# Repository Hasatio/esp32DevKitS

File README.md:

# ESP32-DEVKIT-S

The circuit taken as an example while designing the board [Thing Plus C - ESP32 WROOM](https://www.sparkfun.com/products/retired/18018)

This pcb scaled down using the components in the example schematic

## Revision 0

### Added:

- 1x ADXL345 (Accelerometer)
- 2x 1x20 FPC connector for ESP pins
- In breakable PCB:
  - 4x ADS1115 (Analog to Digital Converter)
  - 1x20 FPC connector
  - 1x QWIIC connector

### Changed:

- ESP32-WROOM-32D model
- Battery socket breakable PCB
- Logo

### Removed:

- RGB led
- SD card

### Note: The connection cannot be made because the tx rx connection paths are not correct.

## Revision 1

- Two circuits were produced for the left and right foot.

### Added:
- New circuit in mirror image design

### Changed:
- Circuit design, components in usb communication and components in the power section
- CH340C model
- TX, RX connection paths reversed
- Analog pull up resistor 100k

### Note: The battery does not charge when the switch is in the off position.

## Revision 2

### Changed:
- The on/off switch will only be used for battery discharge

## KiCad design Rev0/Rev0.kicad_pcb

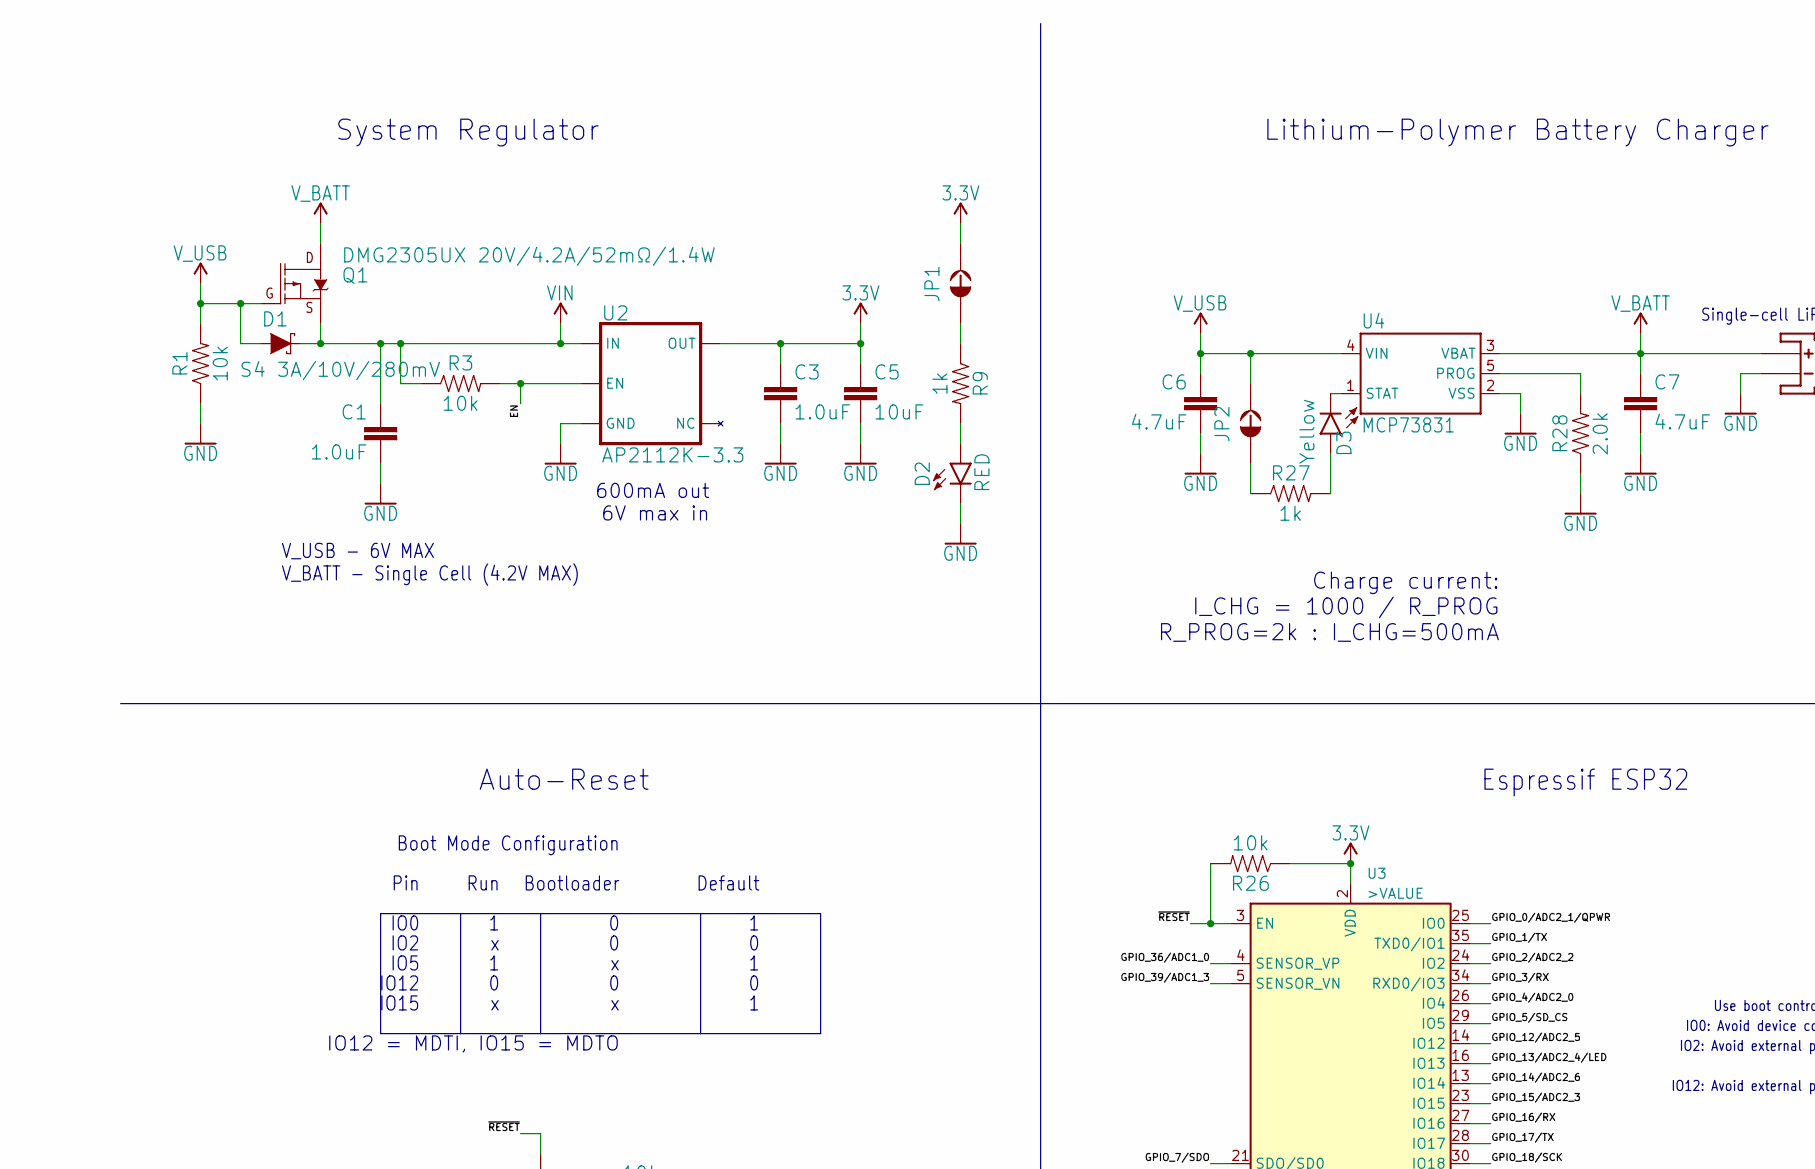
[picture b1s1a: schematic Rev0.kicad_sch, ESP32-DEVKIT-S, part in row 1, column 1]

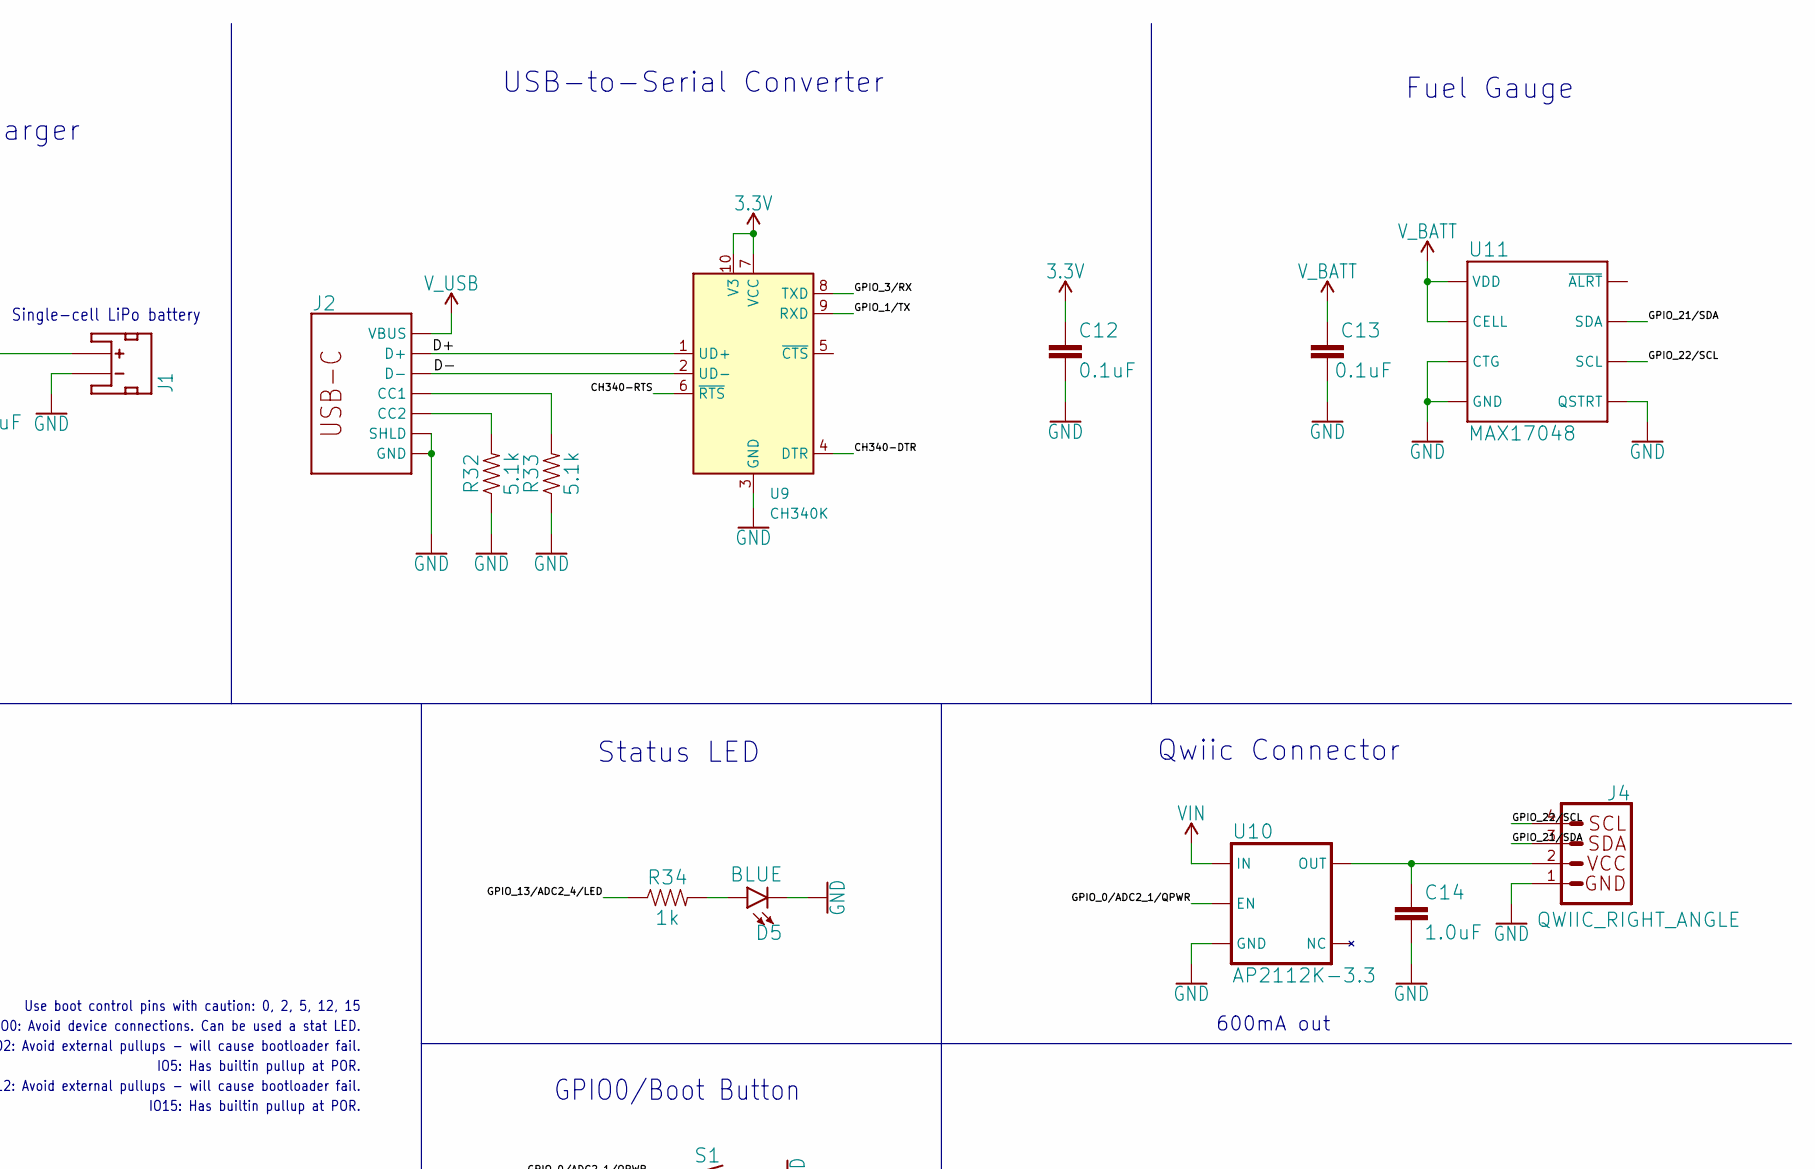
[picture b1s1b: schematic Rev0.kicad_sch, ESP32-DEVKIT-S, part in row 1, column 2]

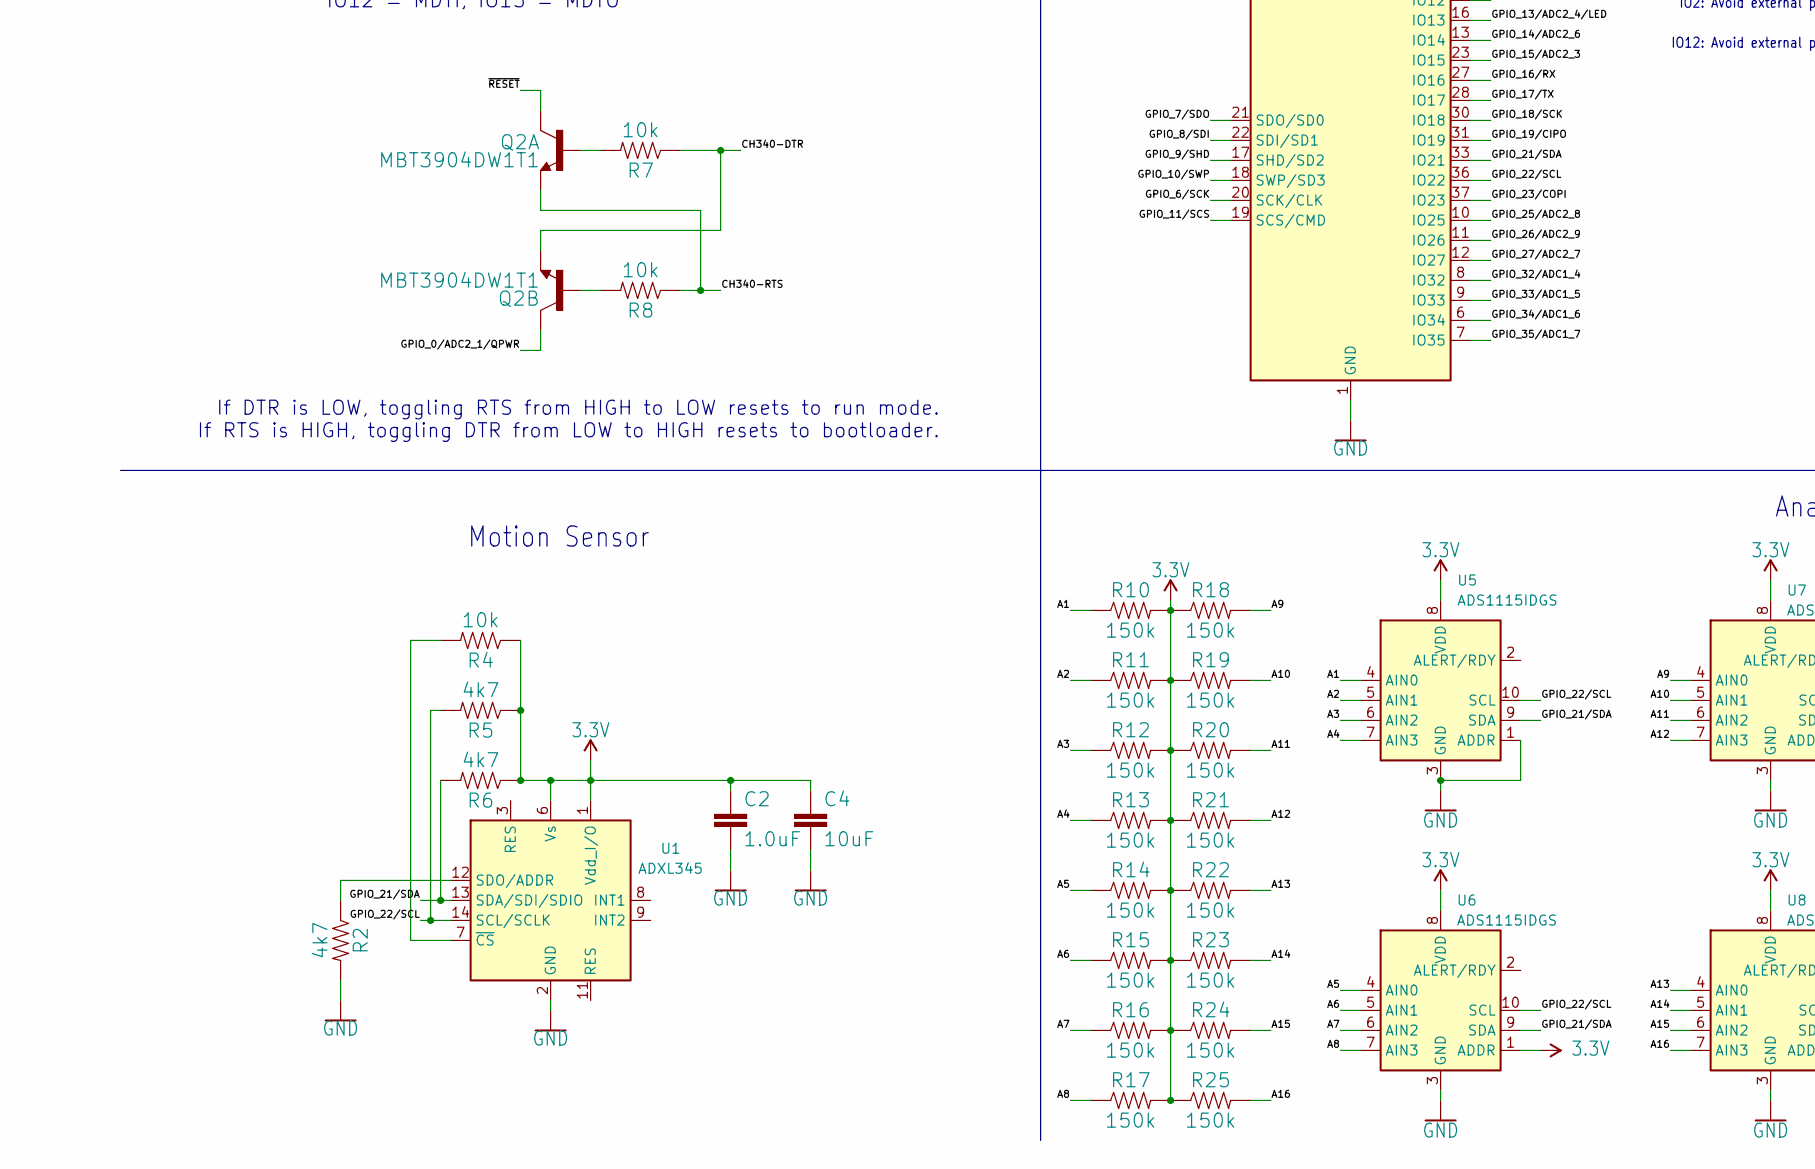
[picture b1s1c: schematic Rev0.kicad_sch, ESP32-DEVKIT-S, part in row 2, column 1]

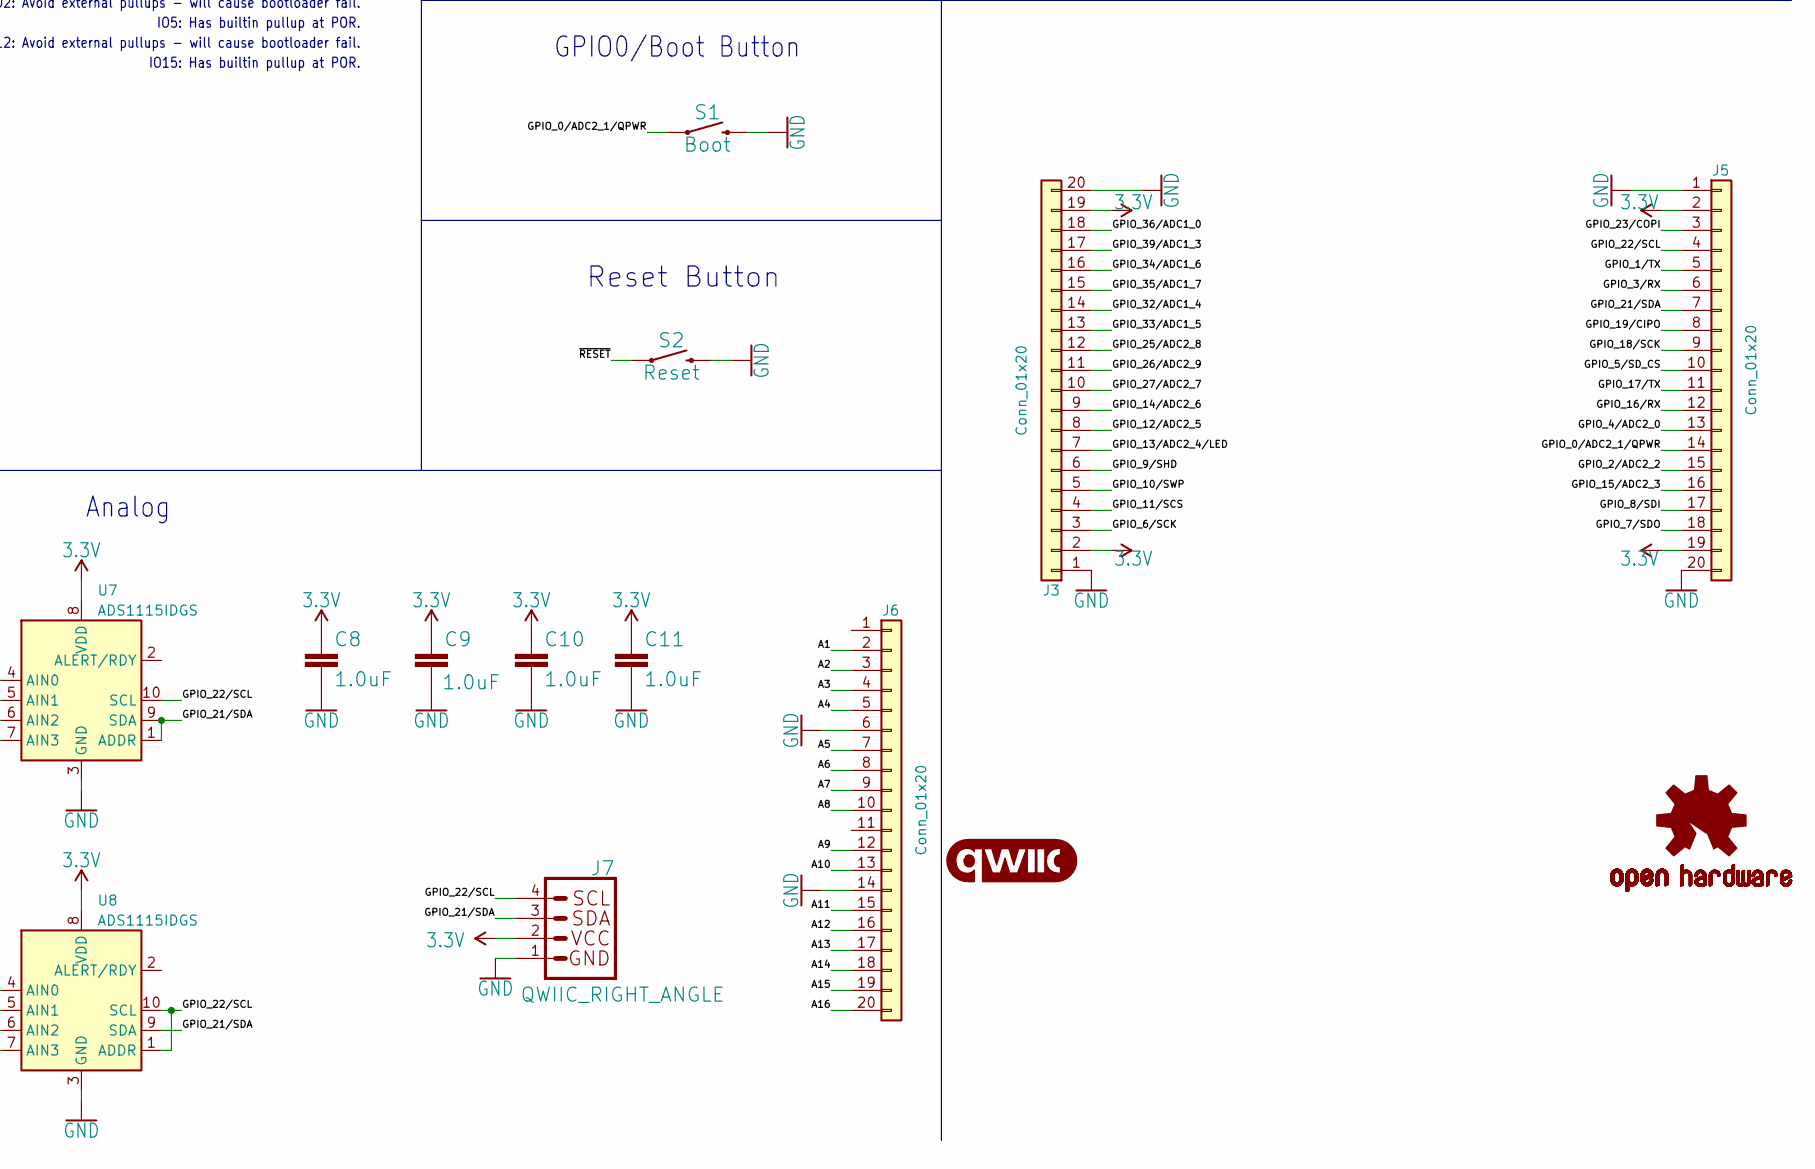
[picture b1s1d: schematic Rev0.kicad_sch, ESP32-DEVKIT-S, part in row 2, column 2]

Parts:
C1, C2, C3, C8, C9, C10, C11, C14: 1.0uF; 0402-TIGHT
C4, C5: 10uF; 0402-TIGHT
C6, C7: 4.7uF; 0402-TIGHT
C12, C13: 0.1uF; 0402-TIGHT
D1: S4 3A/10V/280mV; SOD-323
D2: RED; LED-0603
D3: Yellow; LED-0603
D5: BLUE; LED-0603
J1: JST_2MM_MALE; JST-2-SMD
J2: USB_C_2-LAYER_PADS; USB-C-16P-2LAYER-PADS
J3, J5, J6: Conn_01x20; Molex_200528-0200_1x20-1MP_P1.00mm_Horizontal
J4, J7: QWIIC_RIGHT_ANGLE; JST04_1MM_RA
JP1, JP2: JUMPER-SMT_2_NC_TRACE_SILK; SMT-JUMPER_2_NC_TRACE_SILK
LOGO1: QWIIC_LOGO_4MM; QWIIC_4MM
LOGO2: OSHW-LOGOMINI; OSHW-LOGO-MINI
Q1: DMG2305UX 20V/4.2A/52mΩ/1.4W; SOT23-3
Q2: MBT3904DW1T1; SC70-6
R1, R3, R4, R7, R8, R26: 10k; 0402-TIGHT
R2, R5, R6: 4k7; 0402-TIGHT
R9, R27, R34: 1k; 0402-TIGHT
R10, R11, R12, R13, R14, R15, R16, R17, R18, R19, R20, R21, R22, R23, R24, R25: 150k; 0402-TIGHT
R28: 2.0k; 0402-TIGHT
R32, R33: 5.1k; 0402-TIGHT
S1: Boot; TACTILE_SWITCH_SMD_4.6X2.8MM
S2: Reset; TACTILE_SWITCH_SMD_4.6X2.8MM
U1: ADXL345; LGA-14_3x5mm_P0.8mm_LayoutBorder1x6y
U2, U10: SOT23-5
U3: >VALUE; ESP-WROOM-32-NARROW
U4: MCP73831; SOT23-5
U5, U6, U7, U8: ADS1115IDGS; TSSOP-10_3x3mm_P0.5mm
U9: CH340K; SSOP-10_3.9x4.9mm_P1.00mm
U11: MAX17048; DFN-8

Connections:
3.3V: C2.1, C3.1, C4.1, C5.1, C8.1, C9.1, C10.1, C11.1, C12.1, J3.2, J3.19, J5.2, J5.19, J7.2, JP1.2, R4.1, R5.1, R6.1, R10.2, R11.2, R12.2, R13.2, R14.2, R15.2, R16.2, R17.2, R18.1, R19.1, R20.1, R21.1, R22.1, R23.1, R24.1, R25.1, R26.1, U1.1 (Vdd_I/O), U1.6 (Vs), U2.5 (OUT), U3.2 (VDD), U5.8 (VDD), U6.1 (ADDR), U6.8 (VDD), U7.8 (VDD), U8.8 (VDD), U9.7 (VCC), U9.10 (V3); also elsewhere on the board
/A1: J6.2, R10.1, U5.4 (AIN0); also elsewhere on the board
/A2: J6.3, R11.1, U5.5 (AIN1); also elsewhere on the board
/A3: J6.4, R12.1, U5.6 (AIN2); also elsewhere on the board
/A4: J6.5, R13.1, U5.7 (AIN3); also elsewhere on the board
/A5: J6.7, R14.1, U6.4 (AIN0); also elsewhere on the board
/A6: J6.8, R15.1, U6.5 (AIN1); also elsewhere on the board
/A7: J6.9, R16.1, U6.6 (AIN2); also elsewhere on the board
/A8: J6.10, R17.1, U6.7 (AIN3); also elsewhere on the board
/A9: J6.12, R18.2, U7.4 (AIN0); also elsewhere on the board
/A10: J6.13, R19.2, U7.5 (AIN1); also elsewhere on the board
/A11: J6.15, R20.2, U7.6 (AIN2); also elsewhere on the board
/A12: J6.16, R21.2, U7.7 (AIN3); also elsewhere on the board
/A13: J6.17, R22.2, U8.4 (AIN0); also elsewhere on the board
/A14: J6.18, R23.2, U8.5 (AIN1); also elsewhere on the board
/A15: J6.19, R24.2, U8.6 (AIN2); also elsewhere on the board
/A16: J6.20, R25.2, U8.7 (AIN3); also elsewhere on the board
/CH340-DTR: Q2.1 (E), R7.1, U9.4 (DTR)
/CH340-RTS: Q2.4 (E), R8.1, U9.6 (~RTS)
/D+: J2.A6 (D+), J2.B6 (D+), U9.1 (UD+)
/D-: J2.A7 (D-), J2.B7 (D-), U9.2 (UD-)
/EN: R3.2, U2.3 (EN)
/GPIO_0/ADC2_1/QPWR: J5.14, Q2.6 (C), S1.1, S1.2 (1), U3.25 (IO0), U10.3 (EN); also elsewhere on the board
/GPIO_2/ADC2_2: J5.15, U3.24 (IO2)
/GPIO_4/ADC2_0: J5.13, U3.26 (IO4)
/GPIO_5/SD_CS: J5.10, U3.29 (IO5)
/GPIO_6/SCK: J3.3, U3.20 (SCK/CLK)
/GPIO_7/SDO: J5.18, U3.21 (SDO/SD0)
/GPIO_8/SDI: J5.17, U3.22 (SDI/SD1)
/GPIO_9/SHD: J3.6, U3.17 (SHD/SD2)
/GPIO_10/SWP: J3.5, U3.18 (SWP/SD3)
/GPIO_11/SCS: J3.4, U3.19 (SCS/CMD)
/GPIO_12/ADC2_5: J3.8, U3.14 (IO12)
/GPIO_13/ADC2_4/LED: J3.7, R34.1, U3.16 (IO13)
/GPIO_14/ADC2_6: J3.9, U3.13 (IO14)
/GPIO_15/ADC2_3: J5.16, U3.23 (IO15)
/GPIO_16/RX: J5.12, U3.27 (IO16)
/GPIO_17/TX: J5.11, U3.28 (IO17)
/GPIO_18/SCK: J5.9, U3.30 (IO18)
/GPIO_19/CIPO: J5.8, U3.31 (IO19)
/GPIO_21/SDA: J4.3, J5.7, J7.3, R6.2, U1.13 (SDA/SDI/SDIO), U3.33 (IO21), U5.9 (SDA), U6.9 (SDA), U7.1 (ADDR), U7.9 (SDA), U8.9 (SDA), U11.8 (SDA); also elsewhere on the board
/GPIO_22/SCL: J4.4, J5.4, J7.4, R5.2, U1.14 (SCL/SCLK), U3.36 (IO22), U5.10 (SCL), U6.10 (SCL), U7.10 (SCL), U8.1 (ADDR), U8.10 (SCL), U11.7 (SCL); also elsewhere on the board
/GPIO_23/COPI: J5.3, U3.37 (IO23)
/GPIO_25/ADC2_8: J3.12, U3.10 (IO25)
/GPIO_26/ADC2_9: J3.11, U3.11 (IO26)
/GPIO_27/ADC2_7: J3.10, U3.12 (IO27)
/GPIO_32/ADC1_4: J3.14, U3.8 (IO32)
/GPIO_33/ADC1_5: J3.13, U3.9 (IO33)
/GPIO_34/ADC1_6: J3.16, U3.6 (IO34)
/GPIO_35/ADC1_7: J3.15, U3.7 (IO35)
/GPIO_36/ADC1_0: J3.18, U3.4 (SENSOR_VP)
/GPIO_39/ADC1_3: J3.17, U3.5 (SENSOR_VN)
/~RESET: Q2.3 (C), R26.2, S2.1, S2.2 (1), U3.3 (EN); also elsewhere on the board
GND: C1.2, C2.2, C3.2, C4.2, C5.2, C6.2, C7.2, C8.2, C9.2, C10.2, C11.2, C12.2, C13.2, C14.2, D2.C, D5.C, J1.1 (-), J2.GND, J2.GND2 (GND), J2.SHLD1 (SHLD), J2.SHLD2 (SHLD), J2.SHLD3 (SHLD), J2.SHLD4 (SHLD), J3.1, J3.20, J4.1, J5.1, J5.20, J6.6, J6.14, J7.1, R1.1, R2.2, R28.1, R32.1, R33.1, S1.3 (2), S1.4 (2), S2.3 (2), S2.4 (2), U1.2 (GND), U1.4 (GND), U1.5 (GND), U2.2 (GND), U3.1 (GND), U3.15 (GND), U3.38 (GND), U3.39 (GND), U4.2 (VSS), U5.1 (ADDR), U5.3 (GND), U6.3 (GND), U7.3 (GND), U8.3 (GND), U9.3 (GND), U10.2 (GND), U11.1 (CTG), U11.4 (GND), U11.6 (QSTRT), U11.9 (GND); also elsewhere on the board
unnamed: D2.A, R9.2
unnamed: D3.A, R27.2
unnamed: D5.A, R34.2
unnamed: J2.A5 (CC1), R33.2
unnamed: J2.B5 (CC2), R32.2
unnamed: JP1.1, R9.1
unnamed: JP2.1, R27.1
unnamed: Q2.5 (B), R7.2
unnamed: Q2.2 (B), R8.2
unnamed: R2.1, U1.12 (SDO/ADDR)
unnamed: R4.2, U1.7 (~CS)
unnamed: R28.2, U4.5 (PROG)
unnamed: D3.C, U4.1 (STAT)
unnamed: C14.1, J4.2, U10.5 (OUT)
VIN: C1.1, D1.C, Q1.2 (S), R3.1, U2.1 (IN), U10.1 (IN)
V_BATT: C7.1, C13.1, J1.2 (+), Q1.3 (D), U4.3 (VBAT), U11.2 (CELL), U11.3 (VDD)
V_USB: C6.1, D1.A, J2.VBUS1 (VBUS), J2.VBUS2 (VBUS), JP2.2, Q1.1 (G), R1.2, U4.4 (VIN)

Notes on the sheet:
Fuel Gauge
Auto-Reset
IO15
Boot Mode Configuration
Reset Button
Default
Pin
IO5: Has builtin pullup at POR.
IO5
Run
Qwiic Connector
IO0
V_USB - 6V MAX V_BATT - Single Cell (4.2V MAX)
Lithium-Polymer Battery Charger
IO2
IO12: Avoid external pullups - will cause bootloader fail.
Espressif ESP32
IO12
USB-to-Serial Converter
IO15: Has builtin pullup at POR.
Motion Sensor
Analog
Status LED
Bootloader
Use boot control pins with caution: 0, 2, 5, 12, 15
GPIO0/Boot Button
Charge current: I_CHG = 1000 / R_PROG R_PROG=2k : I_CHG=500mA
Single-cell LiPo battery
IO0: Avoid device connections. Can be used a stat LED.
600mA out
600mA out 6V max in
If DTR is LOW, toggling RTS from HIGH to LOW resets to run mode. If RTS is HIGH, toggling DTR from LOW to HIGH resets to bootloader.
IO2: Avoid external pullups - will cause bootloader fail.
IO12 = MDTI, IO15 = MDTO
System Regulator

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
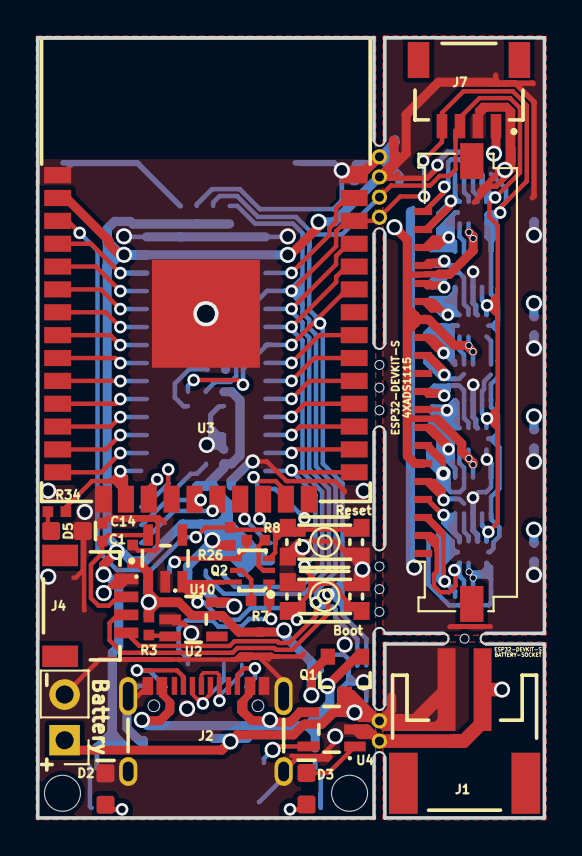
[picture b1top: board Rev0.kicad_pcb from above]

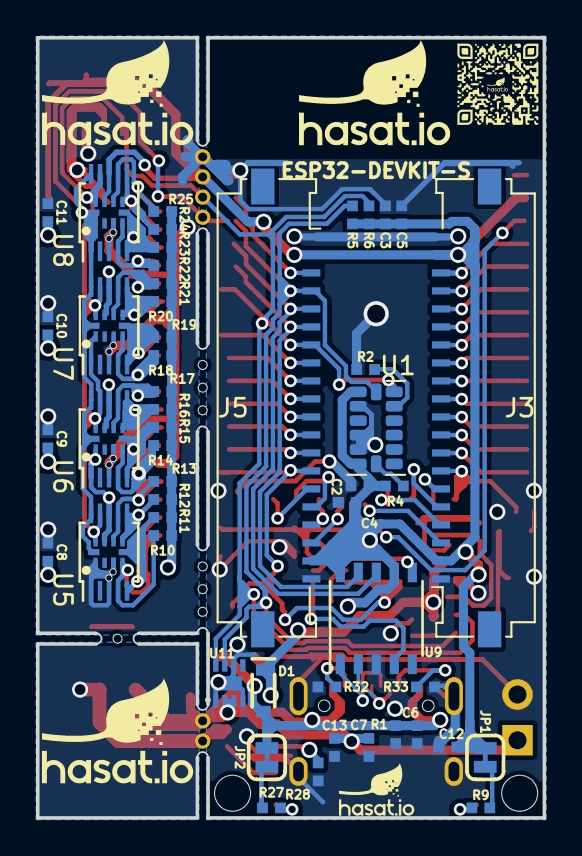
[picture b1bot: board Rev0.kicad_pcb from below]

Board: 2 copper layers, 28.1 x 43.3 mm, 85 parts (54 on the bottom side), 73 nets.

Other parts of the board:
>NAME: >VALUE; TACTILE_SWITCH_SMD_2.8X1.9MM
>NAME#2: >VALUE; TACTILE_SWITCH_SMD_2.8X1.9MM
>NAME#3, >NAME#4, >NAME#5, >NAME#6: >VALUE; QFN-10-RSE
FRAME1: FRAME-LEDGER; CREATIVE_COMMONS
mouse-bite-1mm-slot, mouse-bite-1mm-slot#2: VAL**; mouse-bite-1mm x4
mouse-bite-1mm-slot#3: VAL**; mouse-bite-1mm x2
mouse-bite-1mm-slot#4: VAL**; mouse-bite-1mm 4
mouse-bite-emm-slot: VAL**; mouse-bite-1mm 2

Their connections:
3.3V: >NAME#3.1, >NAME#3.8, >NAME#4.8, >NAME#5.8, >NAME#6.8; also elsewhere on the board
/A1: >NAME#5.4; also elsewhere on the board
/A2: >NAME#5.5; also elsewhere on the board
/A3: >NAME#5.6; also elsewhere on the board
/A4: >NAME#5.7; also elsewhere on the board
/A5: >NAME#3.4; also elsewhere on the board
/A6: >NAME#3.5; also elsewhere on the board
/A7: >NAME#3.6; also elsewhere on the board
/A8: >NAME#3.7; also elsewhere on the board
/A9: >NAME#6.4; also elsewhere on the board
/A10: >NAME#6.5; also elsewhere on the board
/A11: >NAME#6.6; also elsewhere on the board
/A12: >NAME#6.7; also elsewhere on the board
/A13: >NAME#4.4; also elsewhere on the board
/A14: >NAME#4.5; also elsewhere on the board
/A15: >NAME#4.6; also elsewhere on the board
/A16: >NAME#4.7; also elsewhere on the board
/GPIO_0/ADC2_1/QPWR: >NAME.1, >NAME.3; also elsewhere on the board
/GPIO_21/SDA: >NAME#3.9, >NAME#4.9, >NAME#5.9, >NAME#6.1, >NAME#6.9; also elsewhere on the board
/GPIO_22/SCL: >NAME#3.10, >NAME#4.1, >NAME#4.10, >NAME#5.10, >NAME#6.10; also elsewhere on the board
/~RESET: >NAME#2.2, >NAME#2.4; also elsewhere on the board
GND: >NAME.2, >NAME.4, >NAME#2.1, >NAME#2.3, >NAME#3.3, >NAME#4.3, >NAME#5.1, >NAME#5.3, >NAME#6.3; also elsewhere on the board

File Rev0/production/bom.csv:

Designator,Footprint,Quantity,Value,LCSC Part #
"_5, _4, _3, _2, ",,5,,
"C1, C10, C11, C14, C2, C3, C8, C9",0402-TIGHT,8,1.0uF,
"C12, C13",0402-TIGHT,2,0.1uF,
"C4, C5",0402-TIGHT,2,10uF,
"C6, C7",0402-TIGHT,2,4.7uF,
D1,SOD-323,1,S4 3A/10V/280mV,
D2,LED-0603,1,RED,
D3,LED-0603,1,Yellow,
D5,LED-0603,1,BLUE,
FRAME1,CREATIVE_COMMONS,1,FRAME-LEDGER,
J1,JST-2-SMD,1,JST_2MM_MALE,
J2,USB-C-16P-2LAYER-PADS,1,USB_C_2-LAYER_PADS,
"J3, J5, J6",Molex_200528-0200_1x20-1MP_P1.00mm_Horizontal,3,Conn_01x20,
"J4, J7",JST04_1MM_RA,2,QWIIC_RIGHT_ANGLE,
"JP1, JP2",SMT-JUMPER_2_NC_TRACE_SILK,2,JUMPER-SMT_2_NC_TRACE_SILK,
Q1,SOT23-3,1,DMG2305UX 20V/4.2A/52mΩ/1.4W,
Q2,SC70-6,1,MBT3904DW1T1,
"R1, R26, R3, R4, R7, R8",0402-TIGHT,6,10k,
"R10, R11, R12, R13, R14, R15, R16, R17, R18, R19, R20, R21, R22, R23, R24, R25",0402-TIGHT,16,150k,
"R2, R5, R6",0402-TIGHT,3,4k7,
"R27, R34, R9",0402-TIGHT,3,1k,
R28,0402-TIGHT,1,2.0k,
"R32, R33",0402-TIGHT,2,5.1k,
S1,TACTILE_SWITCH_SMD_4.6X2.8MM,1,Boot,
S2,TACTILE_SWITCH_SMD_4.6X2.8MM,1,Reset,
U1,LGA-14_3x5mm_P0.8mm_LayoutBorder1x6y,1,ADXL345,
"U10, U2",SOT23-5,2,AP2112K-3.3,
U11,DFN-8,1,MAX17048,
U3,ESP-WROOM-32-NARROW,1,>VALUE,
U4,SOT23-5,1,MCP73831,
"U5, U6, U7, U8",TSSOP-10_3x3mm_P0.5mm,4,ADS1115IDGS,
U9,SSOP-10_3.9x4.9mm_P1.00mm,1,CH340K,
